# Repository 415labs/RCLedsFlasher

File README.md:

This is a device to blink high power LEDs, used as landing gear strobes on a RC airplane.
Input: +5V/GND/Signal from RX
Output: GND/Led#1/Led#2

When RC signal is over 1.5ms (50% travel), then LEDs blink.

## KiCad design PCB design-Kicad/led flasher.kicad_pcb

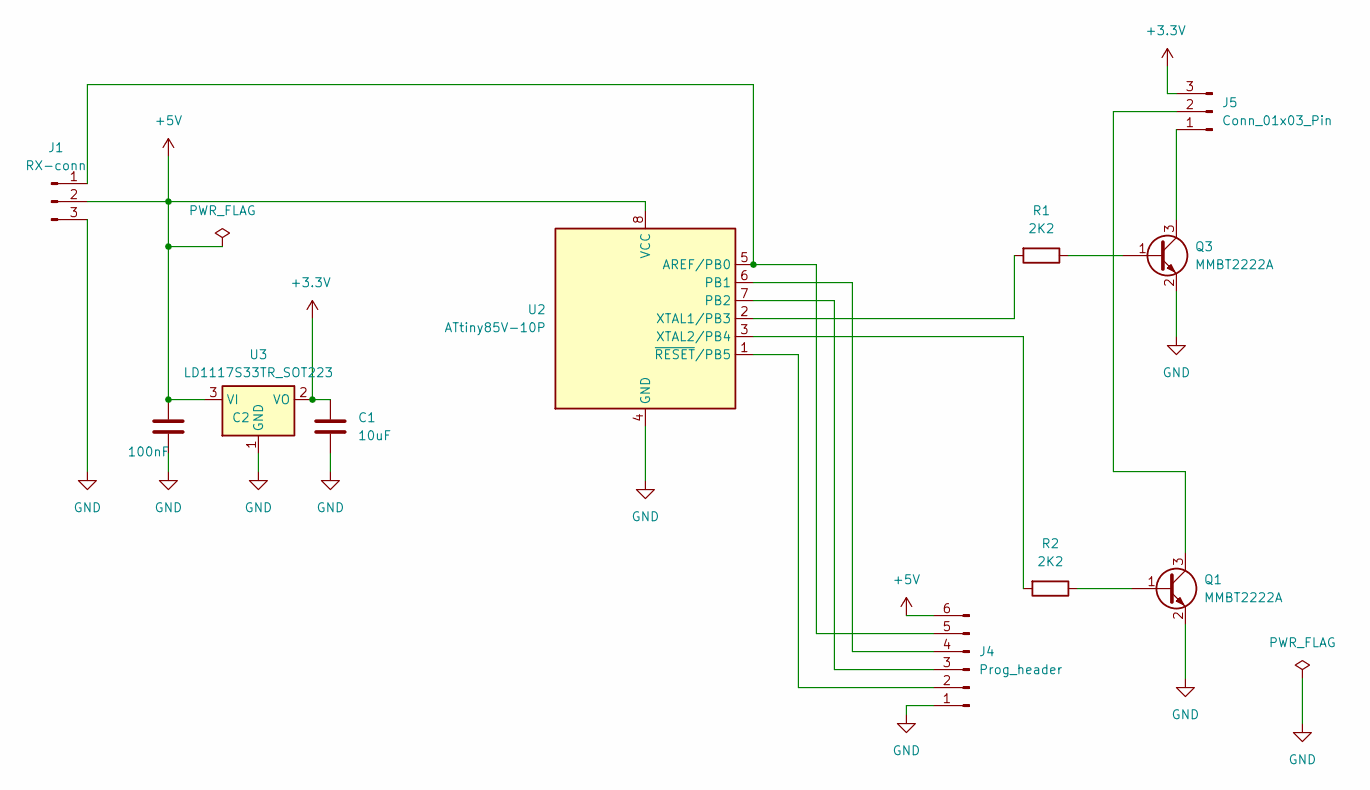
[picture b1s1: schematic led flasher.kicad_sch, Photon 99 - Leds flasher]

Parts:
C1: 10uF; CP_Elec_4x4.5
C2: 100nF; C_0805_2012Metric
J1: RX-conn; PinHeader_1x03_P2.54mm_Horizontal
J4: Prog_header; PinHeader_2x03_P2.54mm_Vertical
J5: Conn_01x03_Pin; PinHeader_1x03_P2.54mm_Horizontal
Q1, Q3: MMBT2222A; SOT-23
R1, R2: 2K2; R_0805_2012Metric
U2: ATtiny85V-10P; SOIC-8W_5.3x5.3mm_P1.27mm
U3: LD1117S33TR_SOT223; SOT-223-3_TabPin2

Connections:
+3.3V: C1.1, J5.3, U3.2 (VO)
+5V: C2.1, J1.2, J4.6, U2.8 (VCC), U3.3 (VI)
GND: C1.2, C2.2, J1.3, J4.1, Q1.2 (E), Q3.2 (E), U2.4 (GND), U3.1 (GND)
unnamed: J1.1, J4.5, U2.5 (AREF/PB0)
unnamed: J4.2, U2.1 (~RESET/PB5)
unnamed: J4.3, U2.7 (PB2)
unnamed: J4.4, U2.6 (PB1)
unnamed: J5.1, Q3.3 (C)
unnamed: J5.2, Q1.3 (C)
unnamed: Q1.1 (B), R2.1
unnamed: Q3.1 (B), R1.1
unnamed: R1.2, U2.2 (XTAL1/PB3)
unnamed: R2.2, U2.3 (XTAL2/PB4)

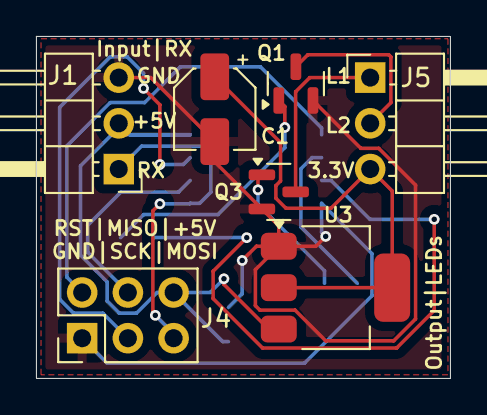
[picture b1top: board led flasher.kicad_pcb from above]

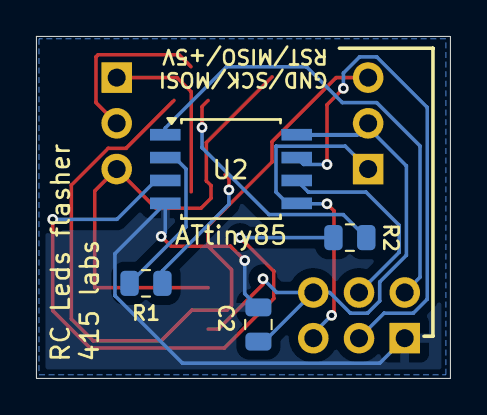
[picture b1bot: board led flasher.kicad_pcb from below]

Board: 2 copper layers, 23.0 x 19.0 mm, 11 parts (4 on the bottom side), 13 nets.

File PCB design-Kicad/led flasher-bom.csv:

"Id";"Designator";"Footprint";"Quantity";"Designation";"Supplier and ref";
1;"U3";"SOT-223-3_TabPin2";1;"LD1117S33TR_SOT223";;;
2;"C1";"CP_Elec_4x4.5";1;"10uF";;;
3;"Q3,Q1";"SOT-23";2;"MMBT2222A";;;
4;"J5";"PinHeader_1x03_P2.54mm_Horizontal";1;"Conn_01x03_Pin";;;
5;"J4";"PinHeader_2x03_P2.54mm_Vertical";1;"Prog_header";;;
6;"J1";"PinHeader_1x03_P2.54mm_Horizontal";1;"RX-conn";;;
7;"C2";"C_0805_2012Metric";1;"100nF";;;
8;"R1,R2";"R_0805_2012Metric";2;"2K2";;;
9;"U2";"SOIC-8W_5.3x5.3mm_P1.27mm";1;"ATtiny85";;;

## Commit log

2024-11-23 first release
2024-11-23 updated BOM
